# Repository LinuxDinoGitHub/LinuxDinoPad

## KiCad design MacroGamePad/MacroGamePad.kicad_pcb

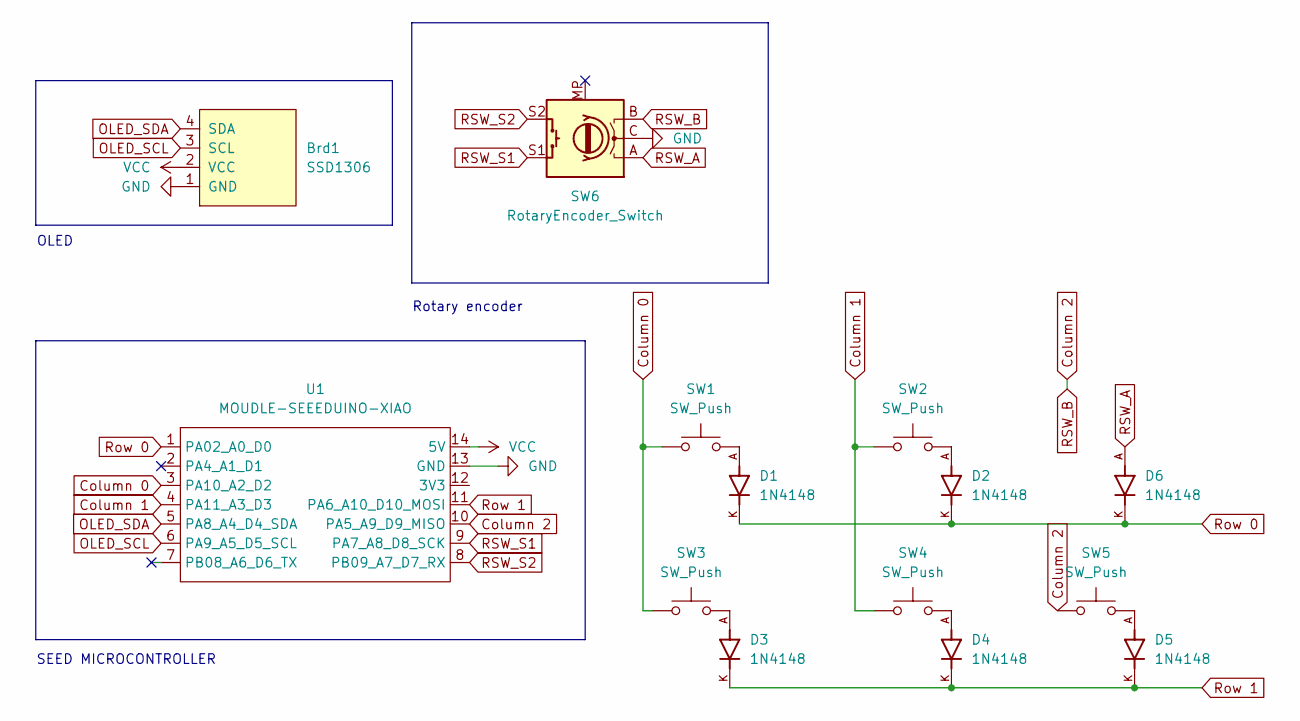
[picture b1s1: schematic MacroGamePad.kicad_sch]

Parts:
Brd1: SSD1306; SSD1306 128x64 OLED
D1, D2, D3, D4, D5, D6: 1N4148; 1N4148 Diode; PARTREV 5
SW1, SW2, SW3, SW4, SW5: SW_Push; SW_Cherry_MX_1.00u_PCB
SW6: RotaryEncoder_Switch; RotaryEncoder_Alps_EC11E-Switch_Vertical_H20mm
U1: MOUDLE-SEEEDUINO-XIAO; XIAO-Generic-Hybrid-14P-2.54-21X17.8MM

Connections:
Column 0: SW1.1, SW3.1, U1.3 (PA10_A2_D2)
Column 1: SW2.1, SW4.1, U1.4 (PA11_A3_D3)
Column 2: SW5.1, SW6.B, U1.10 (PA5_A9_D9_MISO)
GND: Brd1.1 (GND), SW6.C, U1.13 (GND)
unnamed: D1.A, SW1.2
unnamed: D2.A, SW2.2
unnamed: D3.A, SW3.2
unnamed: D4.A, SW4.2
unnamed: D5.A, SW5.2
OLED_SCL: Brd1.3 (SCL), U1.6 (PA9_A5_D5_SCL)
OLED_SDA: Brd1.4 (SDA), U1.5 (PA8_A4_D4_SDA)
RSW_A: D6.A, SW6.A
RSW_S1: SW6.S1, U1.9 (PA7_A8_D8_SCK)
RSW_S2: SW6.S2, U1.8 (PB09_A7_D7_RX)
Row 0: D1.K, D2.K, D6.K, U1.1 (PA02_A0_D0)
Row 1: D3.K, D4.K, D5.K, U1.11 (PA6_A10_D10_MOSI)
VCC: Brd1.2 (VCC), U1.14 (5V)

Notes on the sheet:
SEED MICROCONTROLLER
Rotary encoder
OLED

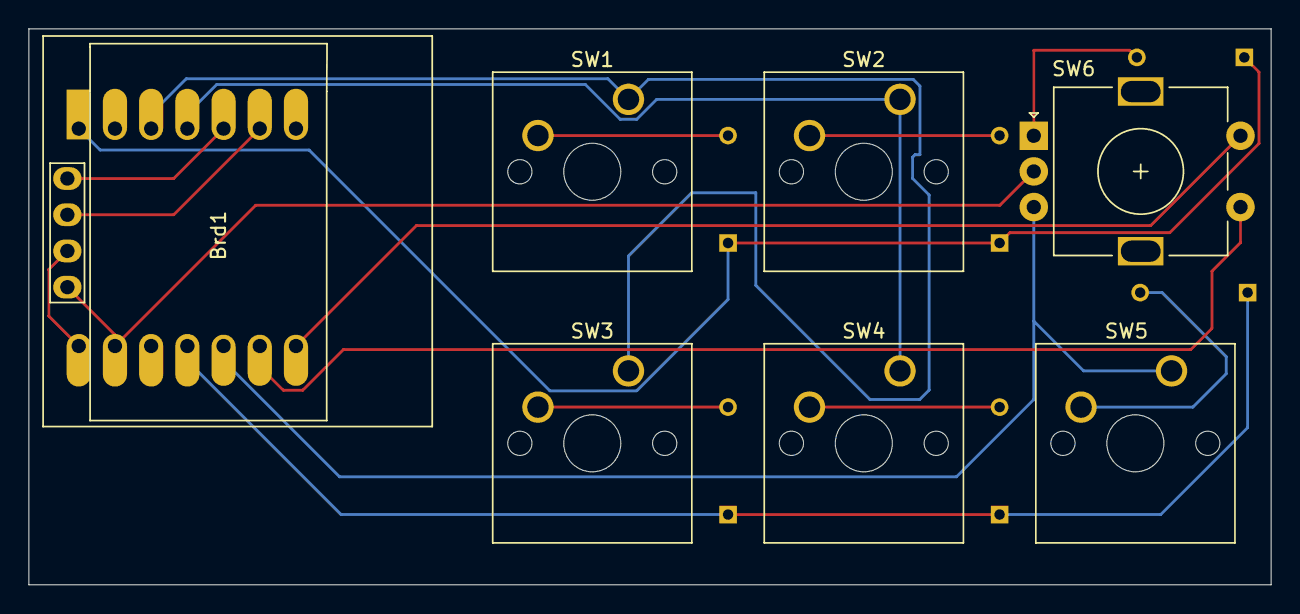
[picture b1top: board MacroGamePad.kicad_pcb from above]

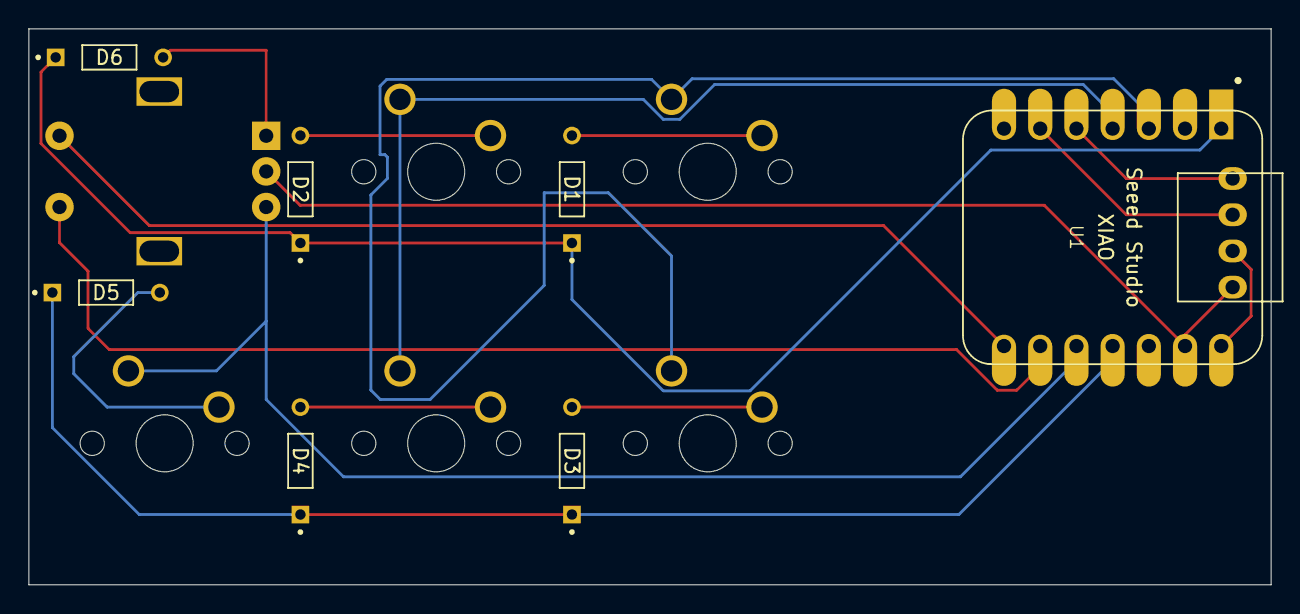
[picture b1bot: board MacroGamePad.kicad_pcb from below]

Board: 2 copper layers, 87.2 x 39.0 mm, 14 parts (7 on the bottom side), 17 nets.

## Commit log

2024-10-18 Initial commit with schematic made
2024-10-18 Added pcb
2024-10-20 PCB finished
